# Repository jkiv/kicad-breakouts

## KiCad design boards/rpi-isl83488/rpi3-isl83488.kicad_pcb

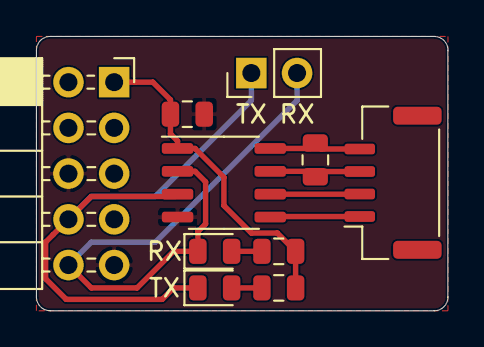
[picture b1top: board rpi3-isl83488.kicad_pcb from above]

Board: 2 copper layers, 22.9 x 15.2 mm, 10 parts (0 on the bottom side), 10 nets.

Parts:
C1: 0.1u; C_0805_2012Metric
D1: TX; LED_0805_2012Metric
D2: RX; LED_0805_2012Metric
J1: RPi; PinSocket_2x05_P2.54mm_Horizontal
J2: JST-GH; JST_GH_SM04B-GHS-TB_1x04-1MP_P1.25mm_Horizontal
J3: SERIAL; PinHeader_1x02_P2.54mm_Vertical
R1: 120R; R_0805_2012Metric
R2, R3: 1k; R_0805_2012Metric
U1: ISL83488; SO-8_3.9x4.9mm_P1.27mm

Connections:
+3V3: C1.1, J1.1, R2.2, R3.2, U1.1
/RX: D2.1, J1.10, J3.2, U1.2
/RX+: J2.4, R1.2, U1.8
/RX-: J2.3, R1.1, U1.7
/TX: D1.1, J1.8, J3.1, U1.3
/TX+: J2.2, U1.6
/TX-: J2.1, U1.5
GND: C1.2, J1.6, J1.9, U1.4
unnamed: D1.2, R2.1
unnamed: D2.2, R3.1
